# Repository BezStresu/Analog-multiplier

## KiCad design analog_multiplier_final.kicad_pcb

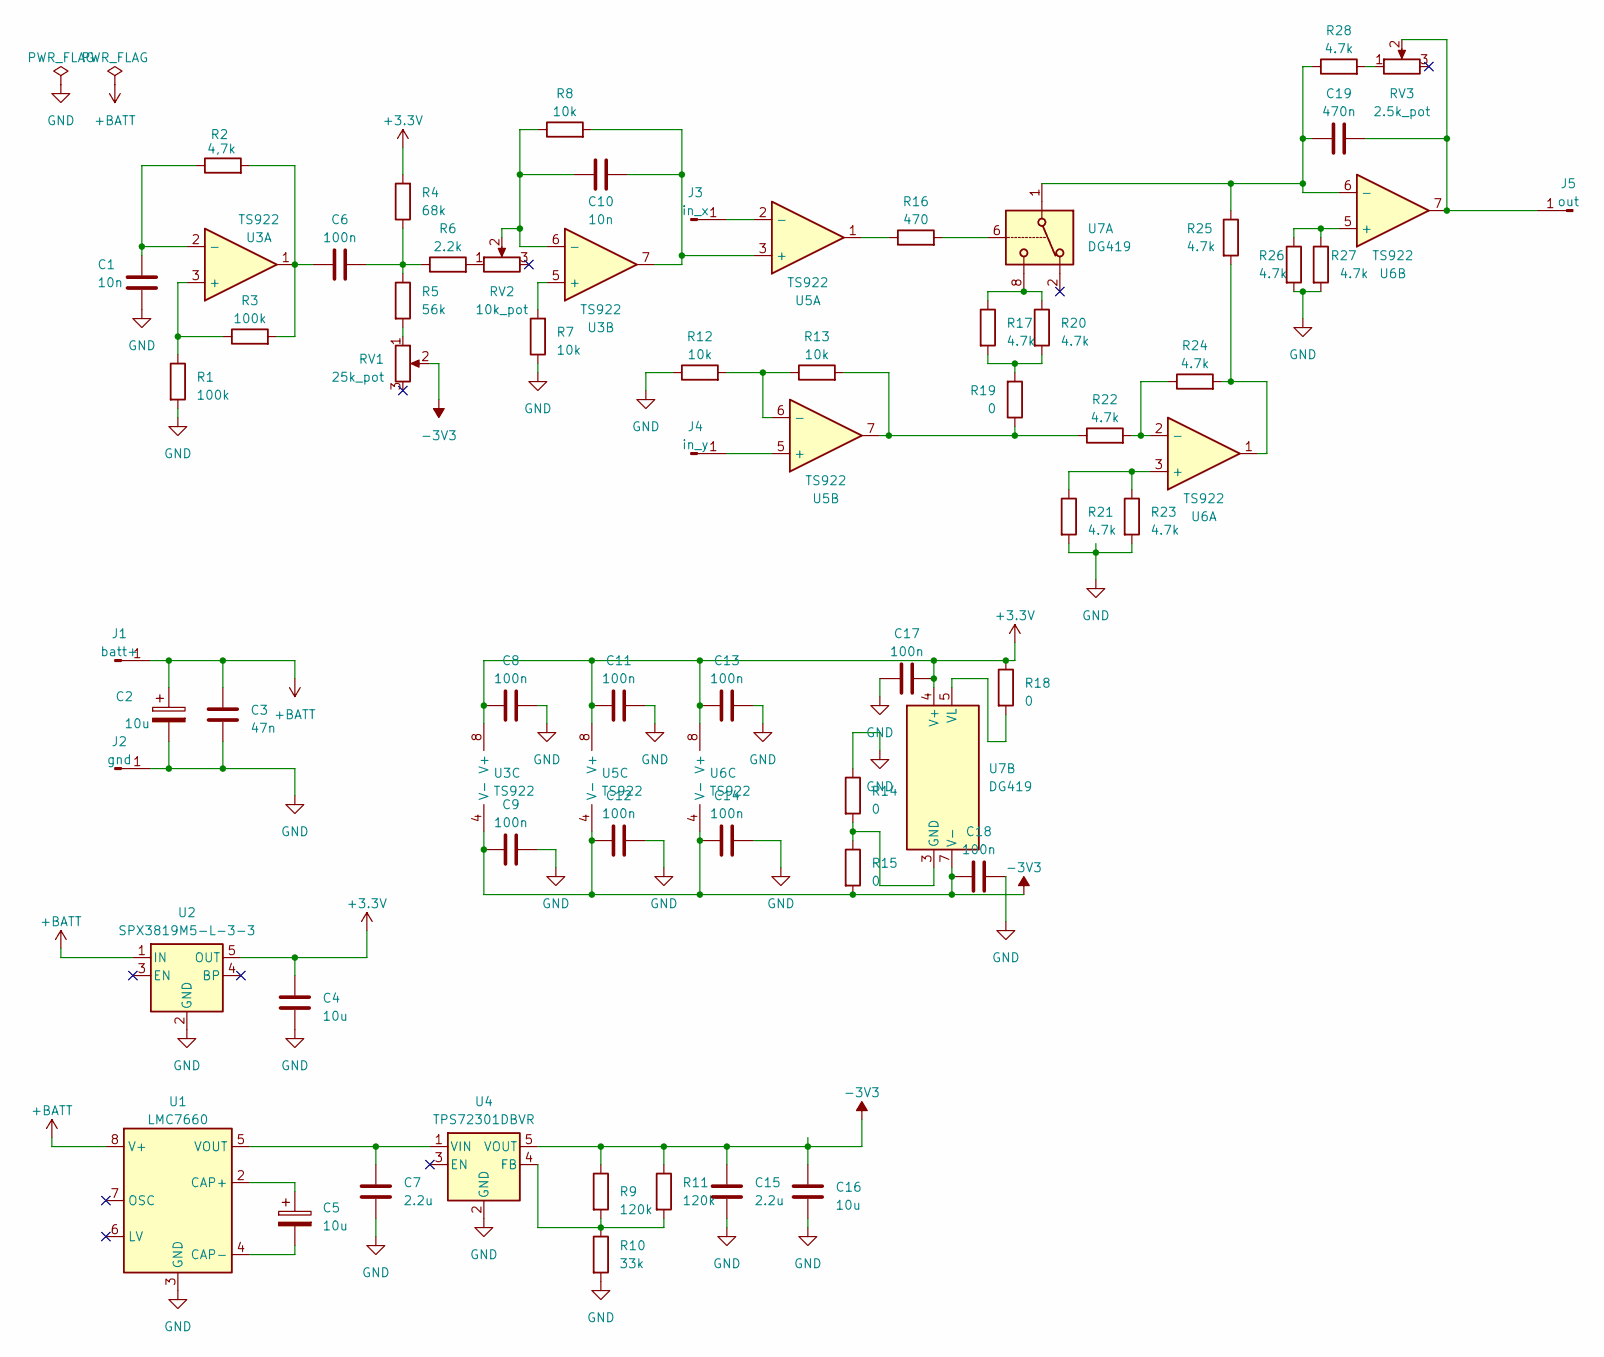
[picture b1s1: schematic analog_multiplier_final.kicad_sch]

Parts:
C1, C10: 10n; C_0805_2012Metric_Pad1.18x1.45mm_HandSolder
C2: 10u; CP_EIA-3528-21_Kemet-B
C3: 47n; C_0805_2012Metric_Pad1.18x1.45mm_HandSolder
C4, C16: 10u; C_0805_2012Metric_Pad1.18x1.45mm_HandSolder
C5: 10u; CP_Elec_4x5.4
C6, C8, C9, C11, C12, C13, C14, C17, C18: 100n; C_0805_2012Metric_Pad1.18x1.45mm_HandSolder
C7, C15: 2.2u; C_0805_2012Metric_Pad1.18x1.45mm_HandSolder
C19: 470n; C_0805_2012Metric_Pad1.18x1.45mm_HandSolder
J1: batt+; TestPoint_Pad_D2.0mm
J2: gnd; TestPoint_Pad_D2.0mm
J3: in_x; TestPoint_Pad_D2.0mm
J4: in_y; TestPoint_Pad_D2.0mm
J5: out; TestPoint_Pad_D2.0mm
R1, R3: 100k; R_0805_2012Metric_Pad1.20x1.40mm_HandSolder
R2: 4,7k; R_0805_2012Metric_Pad1.20x1.40mm_HandSolder
R4: 68k; R_0805_2012Metric_Pad1.20x1.40mm_HandSolder
R5: 56k; R_0805_2012Metric_Pad1.20x1.40mm_HandSolder
R6: 2.2k; R_0805_2012Metric_Pad1.20x1.40mm_HandSolder
R7, R8, R12, R13: 10k; R_0805_2012Metric_Pad1.20x1.40mm_HandSolder
R9, R11: 120k; R_0805_2012Metric_Pad1.20x1.40mm_HandSolder
R10: 33k; R_0805_2012Metric_Pad1.20x1.40mm_HandSolder
R14, R15, R18, R19: 0; R_0805_2012Metric_Pad1.20x1.40mm_HandSolder
R16: 470; R_0805_2012Metric_Pad1.20x1.40mm_HandSolder
R17, R20, R21, R22, R23, R24, R25, R26, R27, R28: 4.7k; R_0805_2012Metric_Pad1.20x1.40mm_HandSolder
RV1: 25k_pot; Potentiometer_ACP_CA6-H2,5_Horizontal
RV2: 10k_pot; Potentiometer_ACP_CA6-H2,5_Horizontal
RV3: 2.5k_pot; Potentiometer_ACP_CA6-H2,5_Horizontal
U1: LMC7660; SOIC-8_3.9x4.9mm_P1.27mm
U2: SPX3819M5-L-3-3; SOT-23-5
U3, U5, U6: TS922; SO-8_5.3x6.2mm_P1.27mm
U4: TPS72301DBVR; SOT-23-5
U7: DG419; SOIC-8_3.9x4.9mm_P1.27mm

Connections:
+3.3V: C4.1, C8.1, C11.1, C13.1, C17.2, R4.2, R18.1, U2.5 (OUT), U3.8 (V+), U5.8 (V+), U6.8 (V+), U7.4 (V+)
+BATT: C2.1, C3.1, J1.1, U1.8 (V+), U2.1 (IN)
-3V3: C9.1, C12.1, C14.1, C15.1, C16.1, C18.1, R9.1, R11.1, R15.2, RV1.2, U3.4 (V-), U4.5 (VOUT), U5.4 (V-), U6.4 (V-), U7.7 (V-)
GND: C1.2, C2.2, C3.2, C4.2, C7.2, C8.2, C9.2, C11.2, C12.2, C13.2, C14.2, C15.2, C16.2, C17.1, C18.2, J2.1, R1.2, R7.1, R10.2, R12.1, R14.1, R21.2, R23.2, R26.2, R27.2, U1.3 (GND), U2.2 (GND), U4.2 (GND)
unnamed: C6.1, R2.2, R3.2, U3.1
unnamed: C6.2, R4.1, R5.1, R6.1
unnamed: J3.1, U5.2 (-)
unnamed: J4.1, U5.5 (+)
unnamed: C19.2, J5.1, RV3.2, U6.7
unnamed: R5.2, RV1.1
unnamed: R6.2, RV2.1
unnamed: R13.2, R19.1, R22.1, U5.7
unnamed: R16.1, U5.1
unnamed: R16.2, U7.6
unnamed: R17.1, R20.1, U7.8
unnamed: R17.2, R19.2, R20.2
unnamed: R24.2, R25.2, U6.1
unnamed: R28.2, RV3.1
unnamed: C5.1, U1.2 (CAP+)
unnamed: C5.2, U1.4 (CAP-)
unnamed: C7.1, U1.5 (VOUT), U4.1 (VIN)
unnamed: R1.1, R3.1, U3.3 (+)
unnamed: C1.1, R2.1, U3.2 (-)
unnamed: R7.2, U3.5 (+)
unnamed: C10.1, R8.1, RV2.2, U3.6 (-)
unnamed: R9.2, R10.1, R11.2, U4.4 (FB)
unnamed: C10.2, R8.2, U3.7, U5.3 (+)
unnamed: R12.2, R13.1, U5.6 (-)
unnamed: R21.1, R23.1, U6.3 (+)
unnamed: R22.2, R24.1, U6.2 (-)
unnamed: R26.1, R27.1, U6.5 (+)
unnamed: C19.1, R25.1, R28.1, U6.6 (-), U7.1
unnamed: R14.2, R15.1, U7.3 (GND)
unnamed: R18.2, U7.5 (VL)

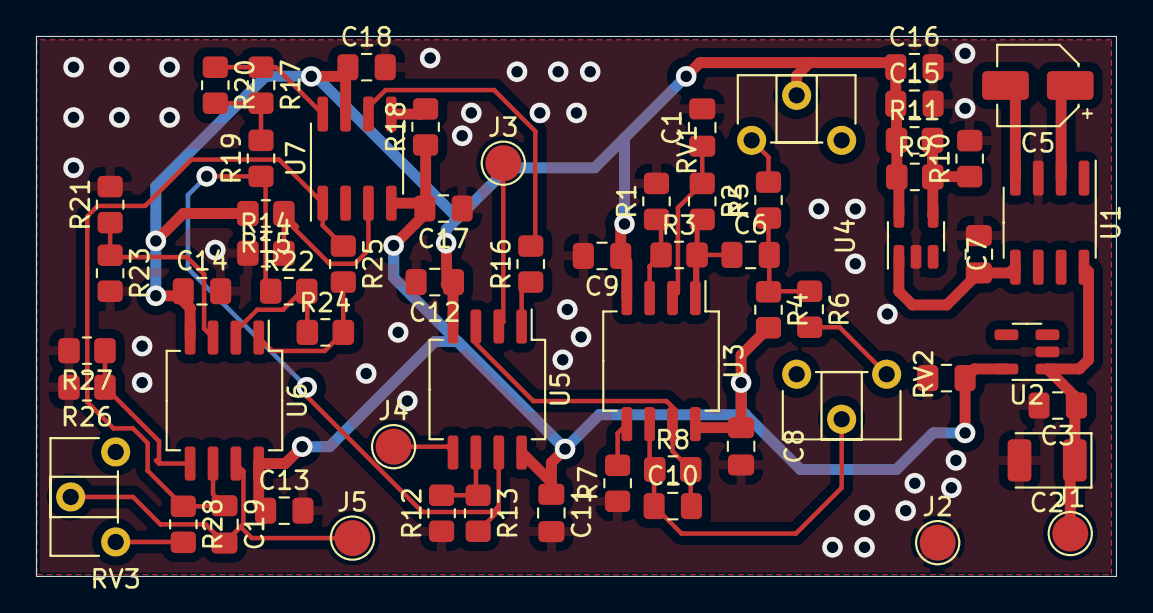
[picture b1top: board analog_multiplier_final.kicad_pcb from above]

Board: 2 copper layers, 60.0 x 30.0 mm, 62 parts (0 on the bottom side), 34 nets.

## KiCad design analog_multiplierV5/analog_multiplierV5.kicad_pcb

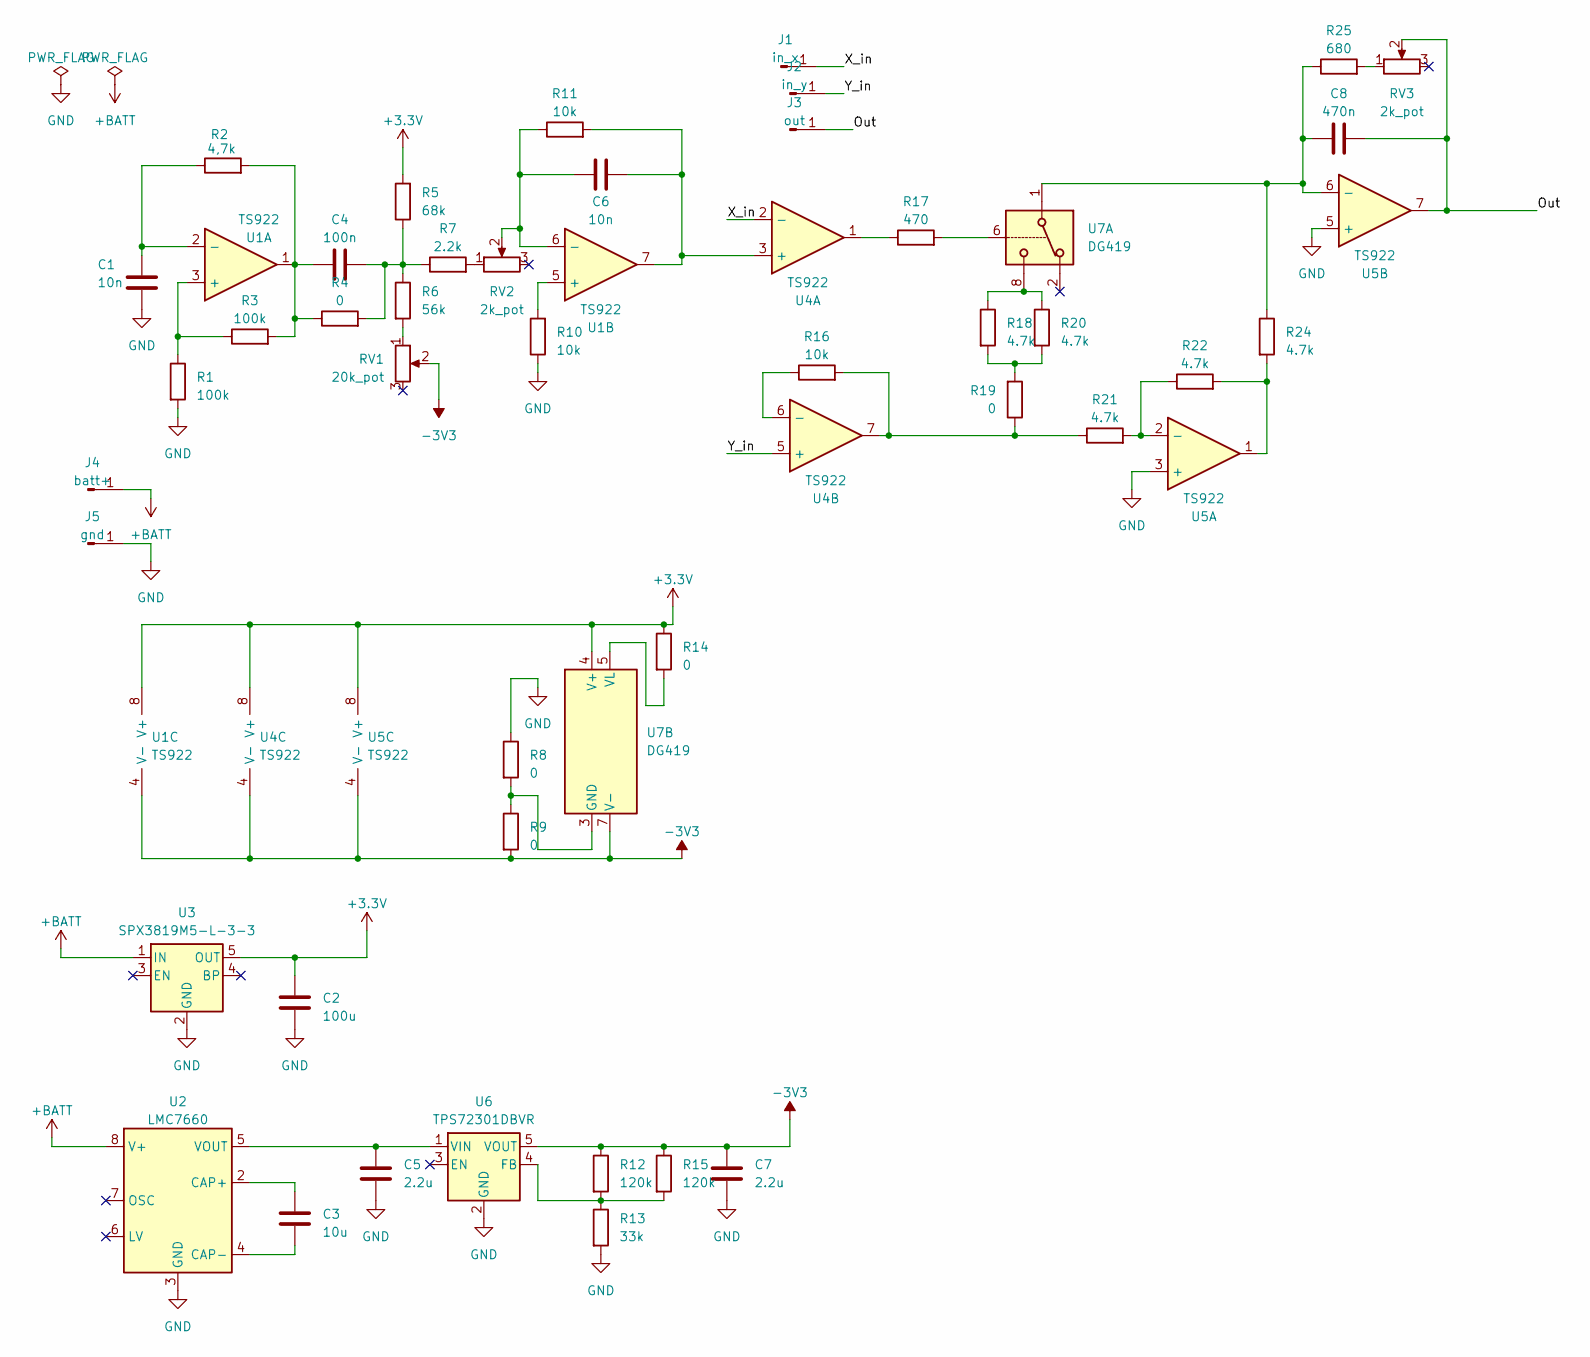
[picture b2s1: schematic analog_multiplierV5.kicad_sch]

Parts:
C1, C6: 10n; C_0805_2012Metric
C2: 100u; C_0805_2012Metric
C3: 10u; C_0805_2012Metric
C4: 100n; C_0805_2012Metric
C5, C7: 2.2u; C_0805_2012Metric
C8: 470n; C_0805_2012Metric
J1: in_x; TestPoint_Pad_D2.0mm
J2: in_y; TestPoint_Pad_D2.0mm
J3: out; TestPoint_Pad_D2.0mm
J4: batt+; TestPoint_Pad_D2.0mm
J5: gnd; TestPoint_Pad_D2.0mm
R1, R3: 100k; R_0805_2012Metric
R2: 4,7k; R_0805_2012Metric
R4, R8, R9, R14, R19: 0; R_0805_2012Metric
R5: 68k; R_0805_2012Metric
R6: 56k; R_0805_2012Metric
R7: 2.2k; R_0805_2012Metric
R10, R11, R16: 10k; R_0805_2012Metric
R12, R15: 120k; R_0805_2012Metric
R13: 33k; R_0805_2012Metric
R17: 470; R_0805_2012Metric
R18, R20, R21, R22, R24: 4.7k; R_0805_2012Metric
R25: 680; R_0805_2012Metric
RV1: 20k_pot; Potentiometer_Piher_PC-16_Single_Horizontal
RV2: 2k_pot; Potentiometer_ACP_CA9-H5_Horizontal
RV3: 2k_pot; Potentiometer_Bourns_3224W_Vertical
U1, U4, U5: TS922; SO-8_5.3x6.2mm_P1.27mm
U2: LMC7660; SOIC-8_3.9x4.9mm_P1.27mm
U3: SPX3819M5-L-3-3; SOT-23-5
U6: TPS72301DBVR; SOT-23-5
U7: DG419; SOIC-8_3.9x4.9mm_P1.27mm

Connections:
+3.3V: C2.1, R5.2, R14.1, U1.8 (V+), U3.5 (OUT), U4.8 (V+), U5.8 (V+), U7.4 (V+)
+BATT: J4.1, U2.8 (V+), U3.1 (IN)
-3V3: C7.1, R9.2, R12.1, R15.1, RV1.2, U1.4 (V-), U4.4 (V-), U5.4 (V-), U6.5 (VOUT), U7.7 (V-)
/Out: C8.2, J3.1, RV3.2, U5.7
/X_in: J1.1, U4.2 (-)
/Y_in: J2.1, U4.5 (+)
GND: C1.2, C2.2, C5.2, C7.2, J5.1, R1.2, R8.1, R10.1, R13.2, U2.3 (GND), U3.2 (GND), U5.3 (+), U5.5 (+), U6.2 (GND)
unnamed: C4.1, R2.2, R3.2, R4.1, U1.1
unnamed: C4.2, R4.2, R5.1, R6.1, R7.1
unnamed: R6.2, RV1.1
unnamed: R7.2, RV2.1
unnamed: R16.2, R19.1, R21.1, U4.7
unnamed: R17.1, U4.1
unnamed: R17.2, U7.6
unnamed: R18.1, R20.1, U7.8
unnamed: R18.2, R19.2, R20.2
unnamed: R22.2, R24.2, U5.1
unnamed: R25.2, RV3.1
unnamed: R1.1, R3.1, U1.3 (+)
unnamed: C1.1, R2.1, U1.2 (-)
unnamed: R10.2, U1.5 (+)
unnamed: C6.1, R11.1, RV2.2, U1.6 (-)
unnamed: C3.1, U2.2 (CAP+)
unnamed: C3.2, U2.4 (CAP-)
unnamed: C5.1, U2.5 (VOUT), U6.1 (VIN)
unnamed: C6.2, R11.2, U1.7, U4.3 (+)
unnamed: R16.1, U4.6 (-)
unnamed: R21.2, R22.1, U5.2 (-)
unnamed: C8.1, R24.1, R25.1, U5.6 (-), U7.1
unnamed: R12.2, R13.1, R15.2, U6.4 (FB)
unnamed: R8.2, R9.1, U7.3 (GND)
unnamed: R14.2, U7.5 (VL)

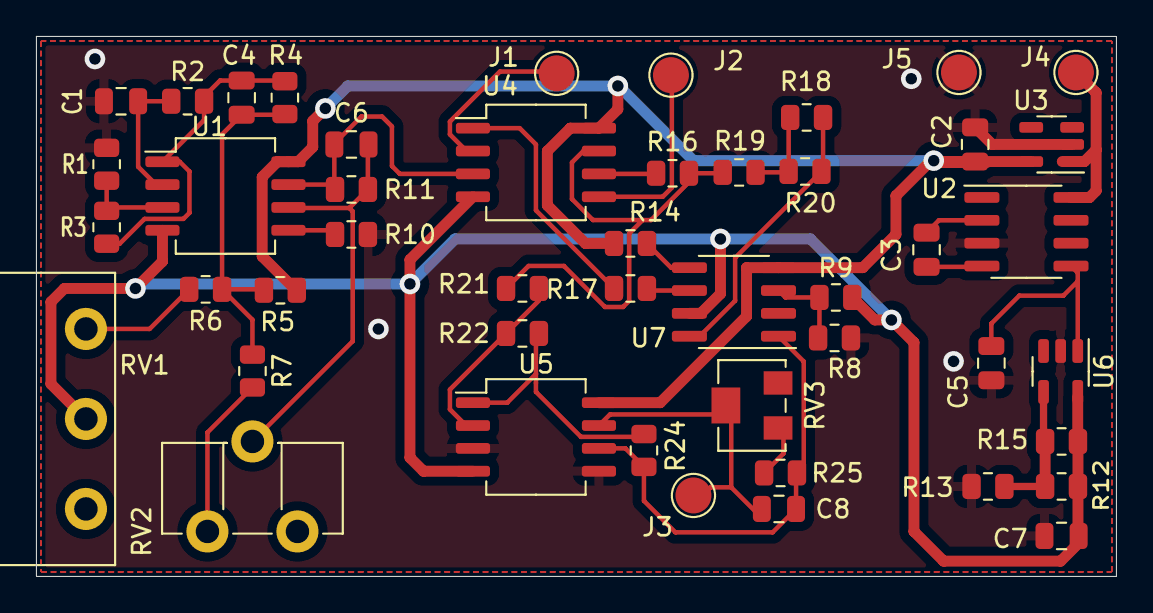
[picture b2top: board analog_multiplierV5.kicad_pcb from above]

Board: 2 copper layers, 60.0 x 30.0 mm, 47 parts (0 on the bottom side), 32 nets.
